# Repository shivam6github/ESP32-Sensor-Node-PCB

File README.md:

# ESP32 Sensor Node (2-Layer Custom PCB)

A compact, manufacturable 2-layer PCB built around the **ESP32-WROOM-32** module, designed in **KiCad**. The board provides regulated 3.3V power, dedicated I2C and SPI sensor interfaces, hardware reset/boot controls, and an external UART programming header.

## Key Features
* **Microcontroller:** ESP32-WROOM-32 with intentional board-edge antenna overhang and RF keep-out zone.
* **Power Supply:** 5V input (`J1`) regulated to 3.3V via an `AMS1117-3.3` LDO (`U2`) with local input/output decoupling (`C1`–`C3`) and a 3.3V power indicator LED (`D1`).
* **Interfaces:**
  * **UART (`J4`):** 4-pin header (`3V3`, `GND`, `TX`, `RX`) for external USB-to-UART flashing and serial debugging.
  * **I2C (`J2`):** 4-pin header (`3V3`, `GND`, `SDA`, `SCL`) with onboard 4.7kΩ pull-up resistors (`R1`, `R2`).
  * **SPI (`J3`):** 6-pin header (`3V3`, `GND`, `SCK`, `MISO`, `MOSI`, `CS`).
* **Controls:** Dedicated tactile `EN` (reset) and `BOOT` (IO0) buttons (`SW1`, `SW2`) for firmware flashing.
* **Mechanical:** 4× symmetrical M3 mounting holes for enclosure or standoff mounting.

## PCB Design Highlights
* **2-Layer Stackup:** Signal routing prioritized on the top layer (`F.Cu`) with a solid, uninterrupted ground pour on the bottom layer (`B.Cu`) to minimize return-path impedance.
* **RF Layout:** ESP32 PCB antenna extends past the `Edge.Cuts` outline with no copper or ground plane underneath.
* **Component Placement:** Decoupling capacitors placed adjacent to the `AMS1117-3.3` and `ESP32` power pins; 0805 SMD passives chosen for reliable hand-soldering and rework.
* **DFM & Verification:** Passed KiCad DRC with **0 errors** and **0 unconnected nets**; complete silkscreen pinout labeling for benchtop bring-up.

## Repository Structure
* `/hardware` — Native KiCad schematic, PCB layout, and project files.
* `/manufacturing` — Fab-ready Gerber & Excellon drill archive (`gerbers.zip`) and Bill of Materials (`BOM.csv`).
* `/docs` — Printable schematic PDF and 3D board renders.

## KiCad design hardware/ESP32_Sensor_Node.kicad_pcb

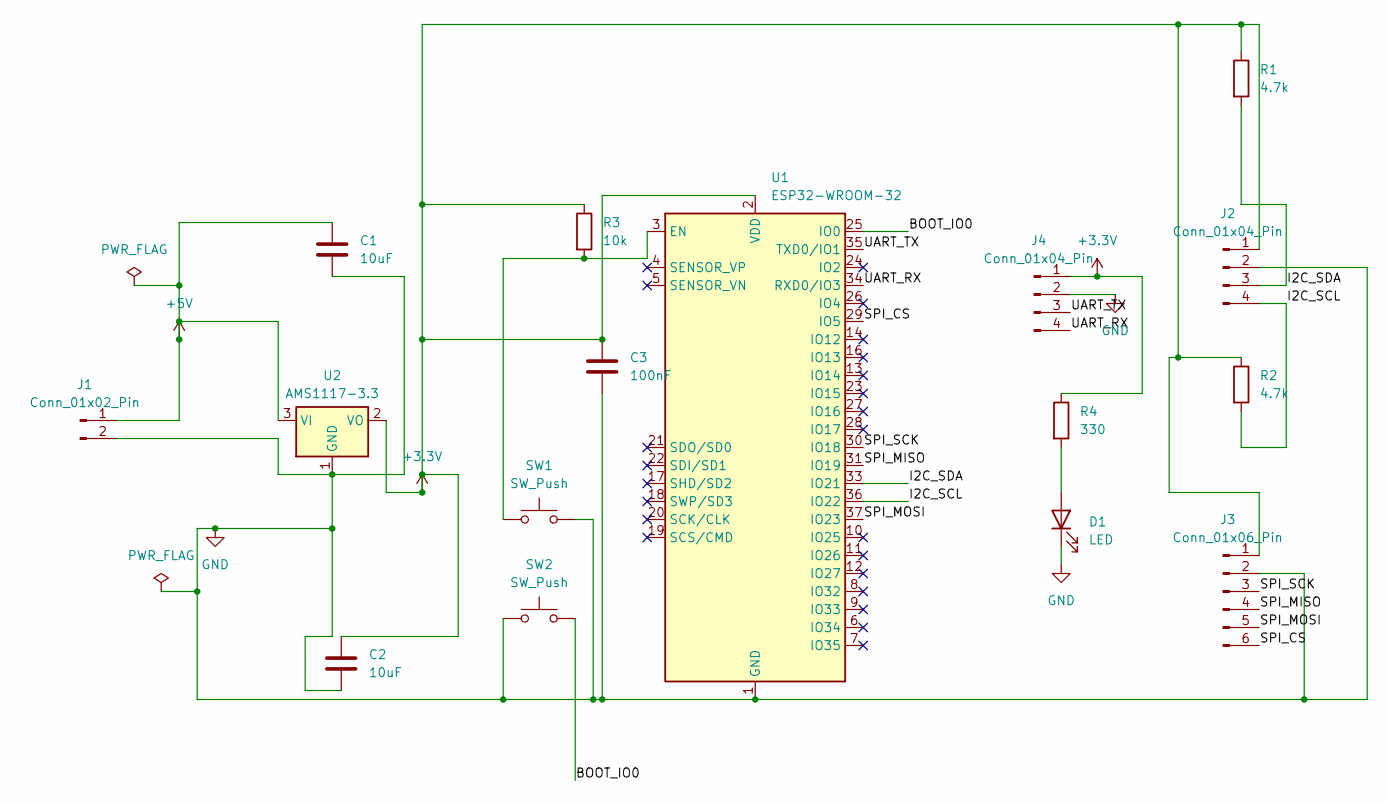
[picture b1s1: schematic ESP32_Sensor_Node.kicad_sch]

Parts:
C1, C2: 10uF; C_0805_2012Metric
C3: 100nF; C_0805_2012Metric
D1: LED; LED_0805_2012Metric
J1: Conn_01x02_Pin; PinHeader_1x02_P2.54mm_Vertical
J2, J4: Conn_01x04_Pin; PinHeader_1x04_P2.54mm_Vertical
J3: Conn_01x06_Pin; PinHeader_1x06_P2.54mm_Vertical
R1, R2: 4.7k; R_0805_2012Metric
R3: 10k; R_0805_2012Metric
R4: 330; LED_0805_2012Metric
SW1, SW2: SW_Push; SW_PUSH_6mm
U1: ESP32-WROOM-32
U2: AMS1117-3.3; SOT-223-3_TabPin2

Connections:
+3.3V: C2.1, C3.1, J2.1, J3.1, J4.1, R1.1, R2.1, R3.1, R4.1, U1.2 (VDD), U2.2 (VO)
+5V: C1.1, J1.1, U2.3 (VI)
/BOOT_IO0: SW2.2, U1.25 (IO0)
/I2C_SCL: J2.4, R2.2, U1.36 (IO22)
/I2C_SDA: J2.3, R1.2, U1.33 (IO21)
/SPI_CS: J3.6, U1.29 (IO5)
/SPI_MISO: J3.4, U1.31 (IO19)
/SPI_MOSI: J3.5, U1.37 (IO23)
/SPI_SCK: J3.3, U1.30 (IO18)
/UART_RX: J4.4, U1.34 (RXD0/IO3)
/UART_TX: J4.3, U1.35 (TXD0/IO1)
GND: C1.2, C2.2, C3.2, D1.1 (K), J1.2, J2.2, J3.2, J4.2, SW1.2, SW2.1, U1.1 (GND), U1.15 (GND), U1.38 (GND), U1.39 (GND), U2.1 (GND)
unnamed: D1.2 (A), R4.2
unnamed: R3.2, SW1.1, U1.3 (EN)

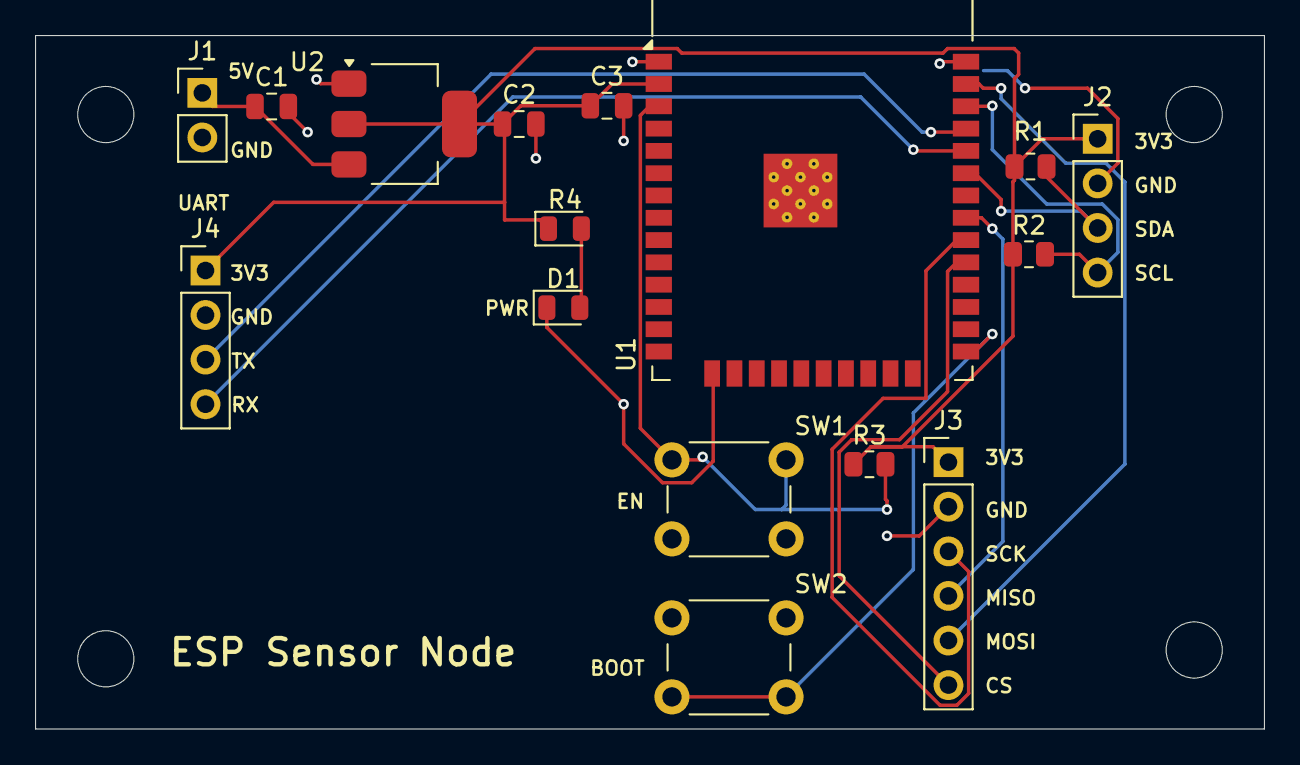
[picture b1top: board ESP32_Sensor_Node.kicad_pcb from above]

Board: 2 copper layers, 70.0 x 39.5 mm, 16 parts (0 on the bottom side), 14 nets.
